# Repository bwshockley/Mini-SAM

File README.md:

# Mini SAM
Mini SAM is a LEGO® minifigure-sized development board based on either the Microchip SAMD51G 48-Pin 32-Bit ARM® Cortex®-M4F MCU (Mini SAM M4) or the Microchip SAMD21G 48-Pin 32-Bit ARM® Cortex®-M0+ MCU running at 48Mhz.

## Board Features

### I/O
The boards includes a usb-micro interface for programming and power.   Around the edge are 0.050" spaced holes with castellations outside of that and the plan is to have a "breakout" board with standard .100" headers.  There is an optional board design in work that will be 4-layer and have the .100" smt header pads included.

The Mini SAM boards include two LED indicators; a standard "Built-In" LED and an APA102 RGB LED.  There are two built-in buttons as well; a RESET button and a user programmable BUTTON.

### Memory
In order to support CircuitPython, a 2MB Quad-SPI flash memory chip is included.  This provides plenty of space for the CircuitPython program as well as space for user programming.

### Other
The boards include a 600mA 3.3V regulator, more than enough to power this little board and its built-in features.  The micro-USB circuitry includes optional provisioning for case grounding and ESD protection.  Finally, The AREF input and recommended Analog and Digital power separation is present on the board.

## BOM
Please see the BOM for each board

## Bootloader
A UF2 bootloader is available for the M4 board (will be available for the M0 when ready).  This bootloader may be built from source using my UF2 repository or downloaded from the [Minifigboards Software](https://www.minifigboards.com/mini-sam-m4/software/) page.

Source: [UF2-SAMDX1](https://github.com/bwshockley/uf2-samdx1) 

## Arduino
Arduino firmware is available for the M4 board as well. Instructions for adding the board to the board manager in the Arduino IDE are available on the [Minifigboards Software](https://www.minifigboards.com/mini-sam-m4/software/) page.

## CircuitPython
CircuitPython is available for the M4 board. [Mini SAM M4](https://circuitpython.org/board/mini_sam_m4/)  
CircuitPython will soon be available for the M0 board.

## Open Source
Boards can be ordered direct from [OSHPark](https://oshpark.com/profiles/bwshockley).

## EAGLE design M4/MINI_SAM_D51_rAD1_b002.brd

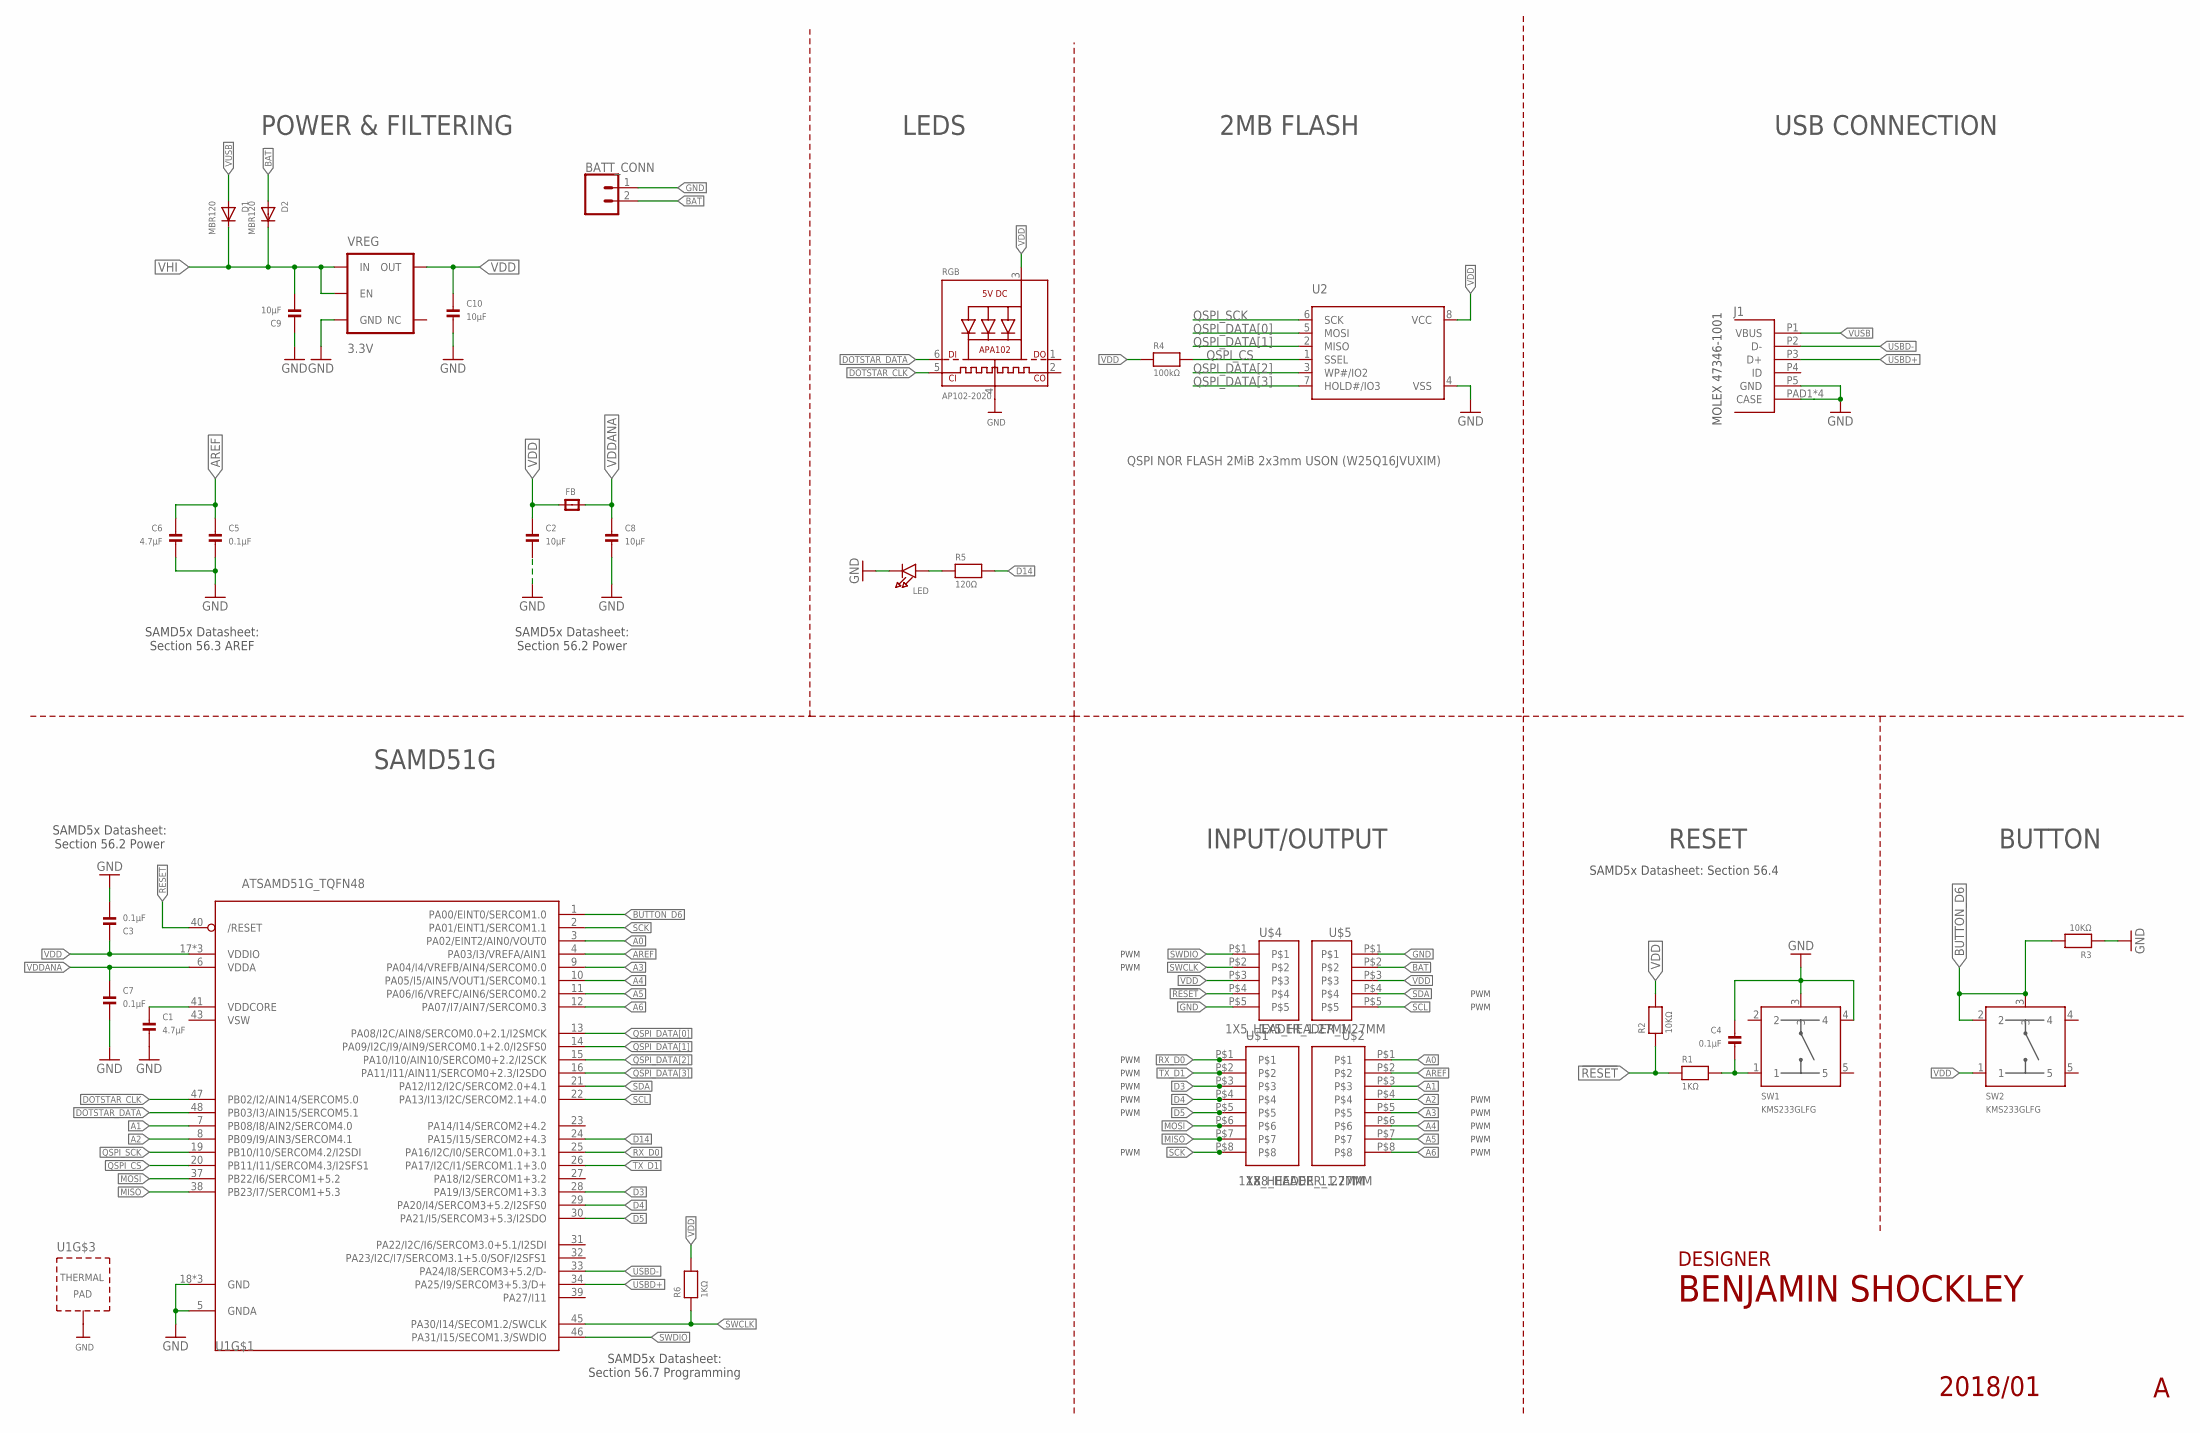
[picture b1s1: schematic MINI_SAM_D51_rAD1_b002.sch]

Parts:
BATT_CONN: CONN_02-JST-2MM-SMT; JST-2-SMD_NO_PASTE
C1, C6: 4.7µF; 0603_CAPACITOR
C2, C8, C9, C10: 10µF; 0603_CAPACITOR
C3, C4, C5, C7: 0.1µF; 0603_CAPACITOR
D1, D2: MBR120; SOD-123FL
FB: Impedence: 50 ohm @ 20 MHz, 220 Ohm @ 100 MHz; lo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; 0603_INDUCTOR
J1: MOLEX_47346-100147346; MOLEX_47346-1001
LED: VLRK31Q1R2-GS08; REVERSE_MOUNT_LED
R1, R6: 1KΩ; 0603_RESISTOR
R2, R3: 10KΩ; 0603_RESISTOR
R4: 100kΩ; 0603_RESISTOR
R5: 120Ω; 0603_RESISTOR
RGB: AP102-2020; APA102_2020
SW1, SW2: KMS233GLFG; KMS_SWITCH
U1: ATSAMD51G_TQFN48; TQFN48_7MM
U2: QSPI NOR FLASH 2MiB 2x3mm USON (W25Q16JVUXIM); USON8
U$1, U$2: 1X8_HEADER_1.27MM
U$4, U$5: 1X5_HEADER_1.27MM
VREG: 3.3V; SOT23-5

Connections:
!RESET: R1.1, R2.1, U1.40 (/RESET), U$4.P$4
A0: U1.3 (PA02/EINT2/AIN0/VOUT0), U$2.P$1
A1: U1.7 (PB08/I8/AIN2/SERCOM4.0), U$2.P$3
A2: U1.8 (PB09/I9/AIN3/SERCOM4.1), U$2.P$4
A3: U1.9 (PA04/I4/VREFB/AIN4/SERCOM0.0), U$2.P$5
A4: U1.10 (PA05/I5/AIN5/VOUT1/SERCOM0.1), U$2.P$6
A5: U1.11 (PA06/I6/VREFC/AIN6/SERCOM0.2), U$2.P$7
A6: U1.12 (PA07/I7/AIN7/SERCOM0.3), U$2.P$8
AREF: C5.1, C6.1, U1.4 (PA03/I3/VREFA/AIN1), U$2.P$2
BAT: BATT_CONN.2 (1), D2.A, U$5.P$2
BUTTON_D6: R3.2, SW2.2, SW2.3, U1.1 (PA00/EINT0/SERCOM1.0)
D3: U1.28 (PA19/I3/SERCOM1+3.3), U$1.P$3
D4: U1.29 (PA20/I4/SERCOM3+5.2/I2SFS0), U$1.P$4
D5: U1.30 (PA21/I5/SERCOM3+5.3/I2SDO), U$1.P$5
D14: R5.2, U1.24 (PA15/I15/SERCOM2+4.3)
DOTSTAR_CLK: RGB.5 (CKI), U1.47 (PB02/I2/AIN14/SERCOM5.0)
DOTSTAR_DATA: RGB.6 (DI), U1.48 (PB03/I3/AIN15/SERCOM5.1)
GND: BATT_CONN.1 (2), C1.2, C2.2, C3.2, C4.1, C5.2, C6.2, C7.2, C8.2, C9.1, C10.2, J1.P5 (GND), J1.PAD1 (CASE), J1.PAD2 (CASE), J1.PAD3 (CASE), J1.PAD4 (CASE), LED.C, R3.1, RGB.4 (GND), SW1.3, SW1.4, U1.5 (GNDA), U1.18 (GND), U1.35 (GND), U1.42 (GND), U1.THERMAL (TP), U2.4 (VSS), U$4.P$5, U$5.P$1, VREG.2 (GND)
MISO: U1.38 (PB23/I7/SERCOM1+5.3), U$1.P$7
MOSI: U1.37 (PB22/I6/SERCOM1+5.2), U$1.P$6
unnamed: LED.A, R5.1
unnamed: C4.2, R1.2, SW1.1
unnamed: C1.1, U1.41 (VDDCORE)
QSPI_CS: R4.2, U1.20 (PB11/I11/SERCOM4.3/I2SFS1), U2.1 (SSEL)
QSPI_DATA[0]: U1.13 (PA08/I2C/AIN8/SERCOM0.0+2.1/I2SMCK), U2.5 (MOSI)
QSPI_DATA[1]: U1.14 (PA09/I2C/I9/AIN9/SERCOM0.1+2.0/I2SFS0), U2.2 (MISO)
QSPI_DATA[2]: U1.15 (PA10/I10/AIN10/SERCOM0+2.2/I2SCK), U2.3 (WP#/IO2)
QSPI_DATA[3]: U1.16 (PA11/I11/AIN11/SERCOM0+2.3/I2SDO), U2.7 (HOLD#/IO3)
QSPI_SCK: U1.19 (PB10/I10/SERCOM4.2/I2SDI), U2.6 (SCK)
RX_D0: U1.25 (PA16/I2C/I0/SERCOM1.0+3.1), U$1.P$1
SCK: U1.2 (PA01/EINT1/SERCOM1.1), U$1.P$8
SCL: U1.22 (PA13/I13/I2C/SERCOM2.1+4.0), U$5.P$5
SDA: U1.21 (PA12/I12/I2C/SERCOM2.0+4.1), U$5.P$4
SWCLK: R6.1, U1.45 (PA30/I14/SECOM1.2/SWCLK), U$4.P$2
SWDIO: U1.46 (PA31/I15/SECOM1.3/SWDIO), U$4.P$1
TX_D1: U1.26 (PA17/I2C/I1/SERCOM1.1+3.0), U$1.P$2
USBD+: J1.P3 (D+), U1.34 (PA25/I9/SERCOM3+5.3/D+)
USBD-: J1.P2 (D-), U1.33 (PA24/I8/SERCOM3+5.2/D-)
VDD: C2.1, C3.1, C10.1, FB.1, R2.2, R4.1, R6.2, RGB.3 (VDD), SW2.1, U1.17 (VDDIO), U1.36 (VDDIO), U1.44 (VDDIO), U2.8 (VCC), U$4.P$3, U$5.P$3, VREG.5 (OUT)
VDDANA: C7.1, C8.1, FB.2, U1.6 (VDDA)
VHI: C9.2, D1.C, D2.C, VREG.1 (IN), VREG.3 (EN)
VSW: U1.43 (VSW)
VUSB: D1.A, J1.P1 (VBUS)

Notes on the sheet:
INPUT/OUTPUT
RESET
POWER & FILTERING
SAMD51G
LEDS
USB CONNECTION
MOLEX 47346-1001
BUTTON
DESIGNER
SAMD5x Datasheet: Section 56.4
2MB FLASH
SAMD5x Datasheet: Section 56.3 AREF
SAMD5x Datasheet: Section 56.2 Power
SAMD5x Datasheet: Section 56.7 Programming
PWM

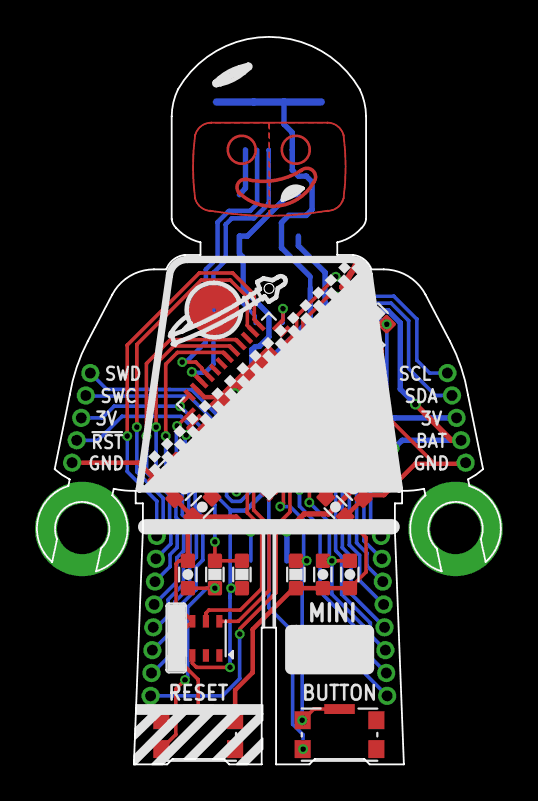
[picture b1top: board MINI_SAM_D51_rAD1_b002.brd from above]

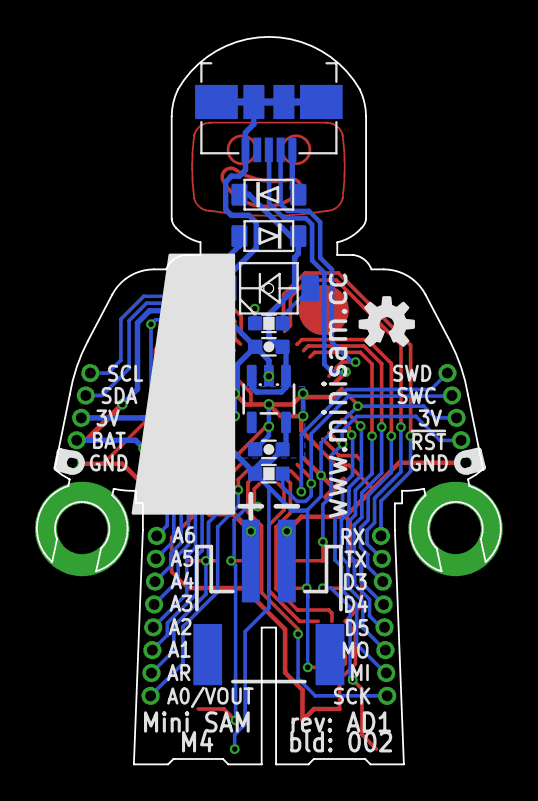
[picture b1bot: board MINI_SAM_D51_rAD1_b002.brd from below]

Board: 2 copper layers, 25.8 x 40.4 mm, 33 parts (11 on the bottom side), 42 nets.

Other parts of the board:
U$3: OSHW-LOGO-S

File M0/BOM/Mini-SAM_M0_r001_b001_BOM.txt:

Qty Value                                                            Device                Package                       Parts           Description                                 PROD_ID    VALUE
4   0.1µF                                                            CAP_CERAMIC_0603MP    _0603MP                       C3, C4, C6, C8  Ceramic Capacitors                                          
1   100kO                                                            RESISTOR_0603MP       _0603MP                       R4              Resistors                                                   
2   10KO                                                             RESISTOR_0603MP       _0603MP                       R2, R3          Resistors                                                   
4   10µF                                                             CAP_CERAMIC_0603MP    _0603MP                       C2, C7, C9, C10 Ceramic Capacitors                                          
2   1KO                                                              RESISTOR_0603MP       _0603MP                       R1, R6          Resistors                                                   
2   1X5_HEADER_1.27MMCAST                                            1X5_HEADER_1.27MMCAST 1X5_HEADER_1.27MM_CASTELLATED J2, J4                                                                      
2   1X8_HEADER_1.27MMCAST                                            1X8_HEADER_1.27MMCAST 1X8_HEADER_1.27MM_CASTELLATED J3, J5                                                                      
1   220O                                                             RESISTOR_0603MP       _0603MP                       R5              Resistors                                                   
2   4.7µF                                                            CAP_CERAMIC_0603MP    _0603MP                       C1, C5          Ceramic Capacitors                                          
1   AP102-2020                                                       APA1022020            APA102_2020                   RGB             APA102/DotStar Pixels                                       
1   AP2112K-3.3V                                                     V_REG_AP2112K-3.3V    SOT23-5                       VREG            AP2112 - 600mA CMOS LDO Regulator w/ Enable VREG-12457 3.3V 
1   ATSAMD21G18                                                      ATSAMD21G_QFN         TQFN48_7MM                    U1                                                                          
1   Easily mounted up-sdie down.                                     LED0805_NOOUTLINE     CHIPLED_0805_NOOUTLINE        LED             LED                                                         
1   Impedence: 50 ohm @ 20 MHz, 220 Ohm @ 100 MHz; low DC resistance FERRITE_0603MP        _0603MP                       FB              Ferrite Bead                                                
2   KMS233GLFG                                                       KMS_SWITCHKMS         KMS_SWITCH                    SW1, SW2                                                                    
2   MBR120                                                           DIODE_SOD-123FL       SOD-123FL                     D1, D2          Diode                                                       
1   MOLEX_47346-100147346                                            MOLEX_47346-100147346 MOLEX_47346-1001              J1                                                                          
1   flash                                                            SPIFLASH_8PINUX       USON8                         U3              SOIC8 SPI Flash

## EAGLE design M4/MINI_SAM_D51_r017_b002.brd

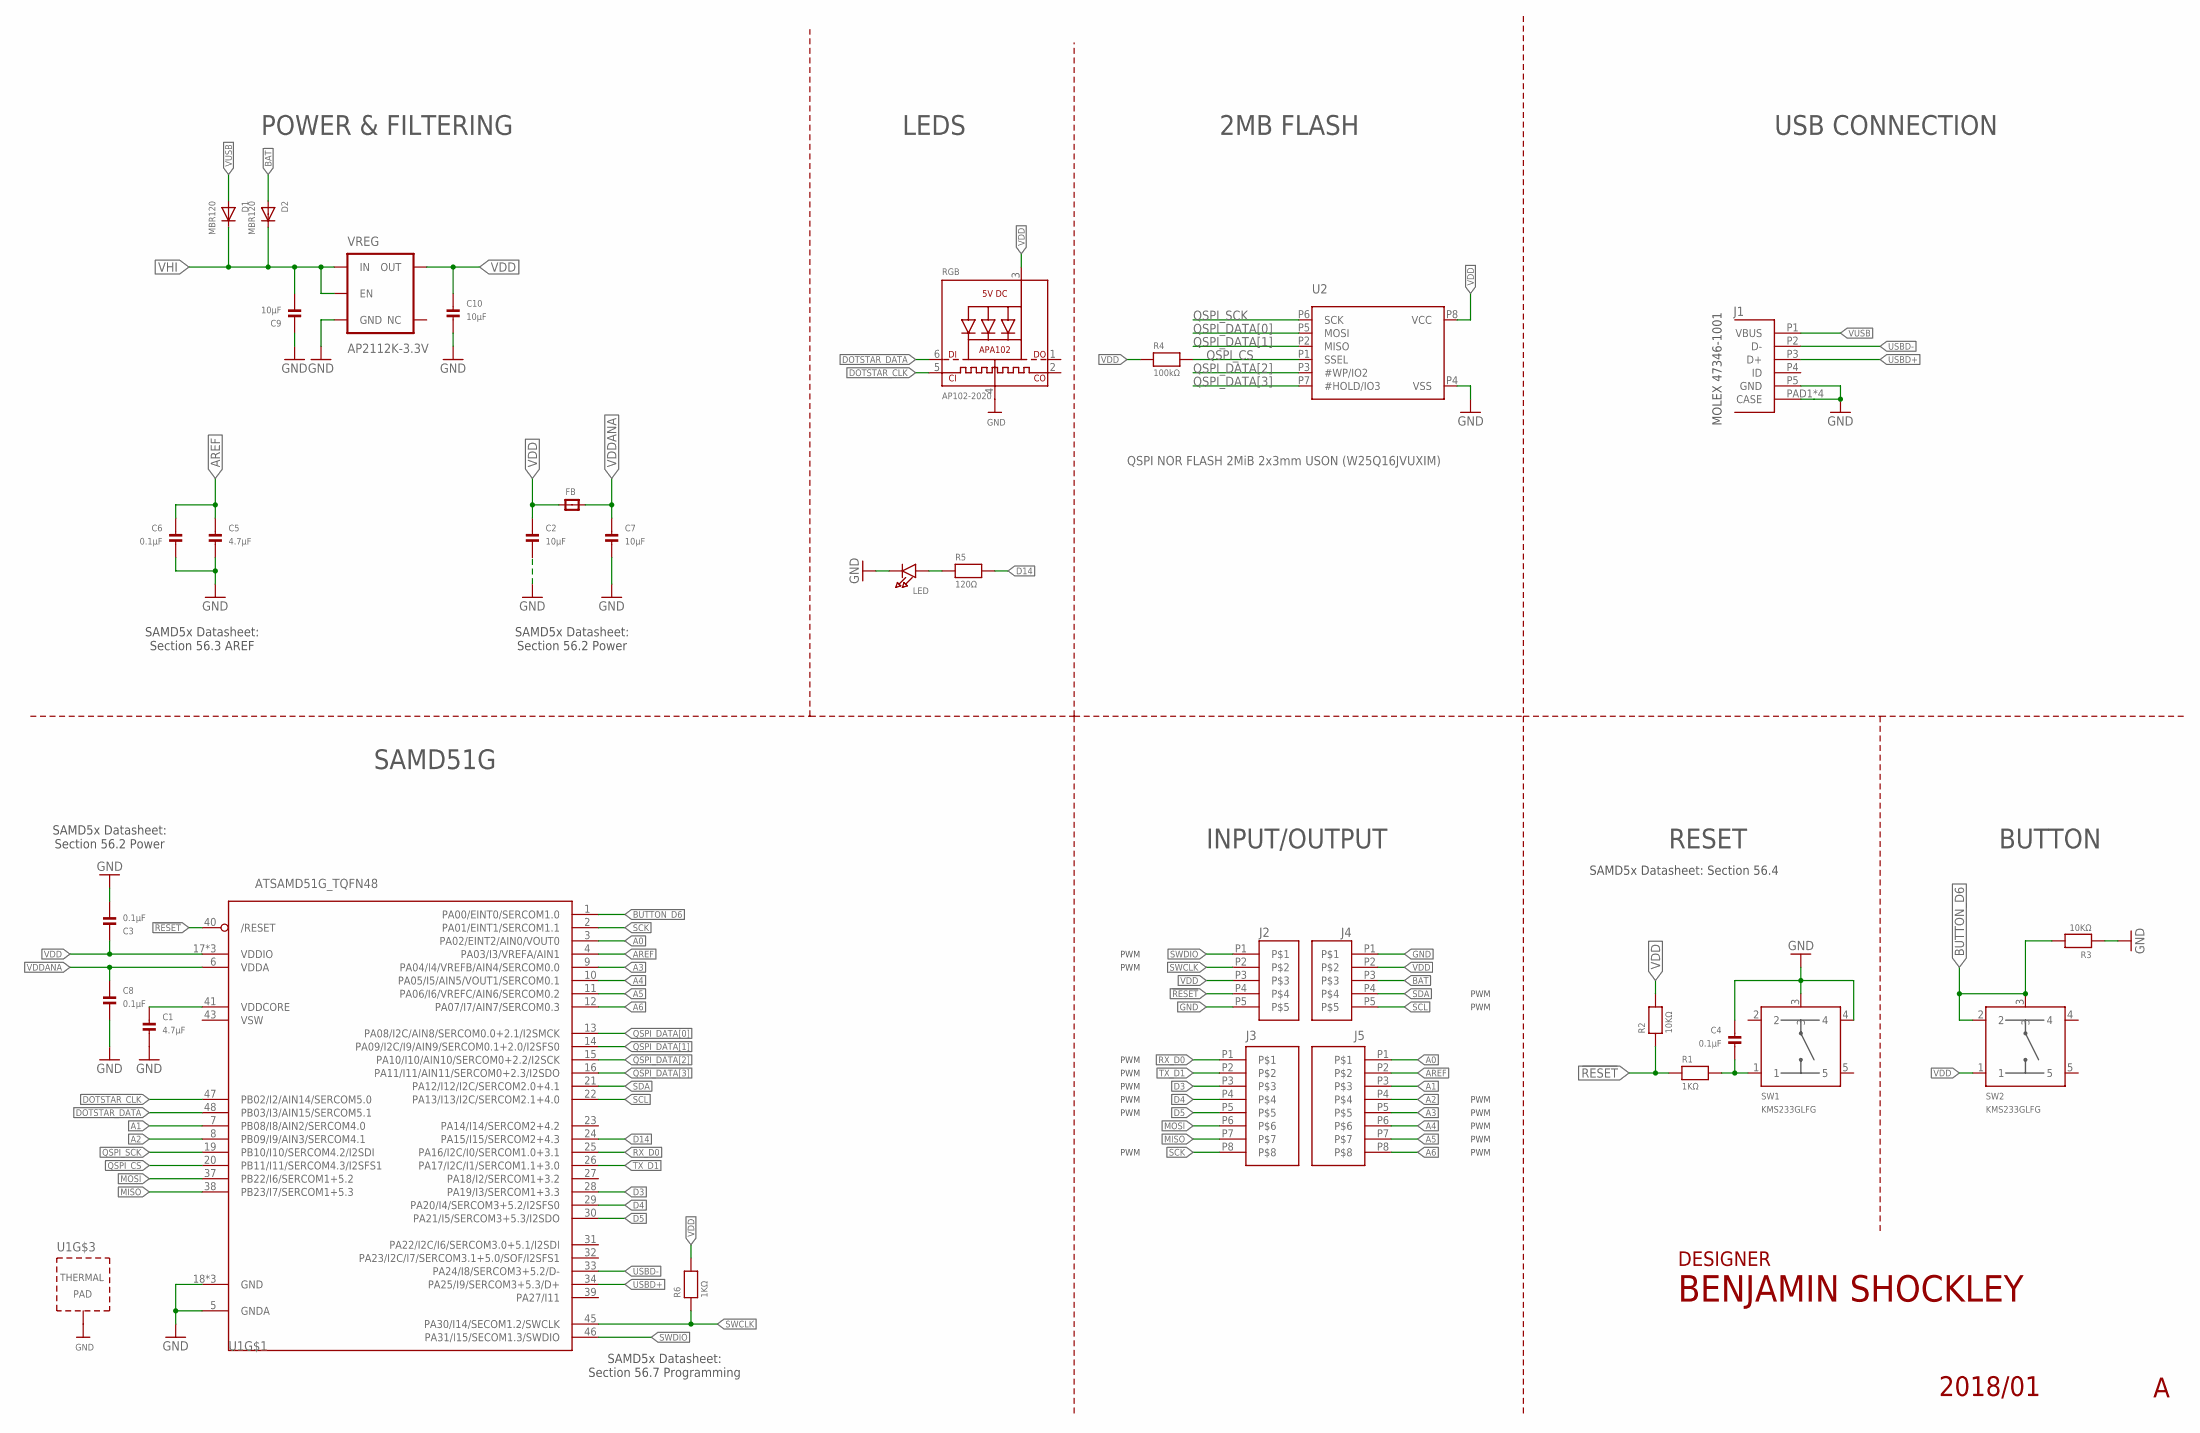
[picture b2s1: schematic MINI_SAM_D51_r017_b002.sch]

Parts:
C1, C5: 4.7µF; _0603MP
C2, C7, C9, C10: 10µF; _0603MP
C3, C4, C6, C8: 0.1µF; _0603MP
D1, D2: MBR120; SOD-123FL
FB: Impedence: 50 ohm @ 20 MHz, 220 Ohm @ 100 MHz; lo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; _0603MP
J1: MOLEX_47346-100147346; MOLEX_47346-1001
J2, J4: 1X5_HEADER_1.27MMCAST; 1X5_HEADER_1.27MM_CASTELLATED
J3, J5: 1X8_HEADER_1.27MMCAST; 1X8_HEADER_1.27MM_CASTELLATED
LED: VLRK31Q1R2-GS08; REVERSE_MOUNT_LED
R1, R6: 1KΩ; _0603MP
R2, R3: 10KΩ; _0603MP
R4: 100kΩ; _0603MP
R5: 120Ω; _0603MP
RGB: AP102-2020; APA102_2020
SW1, SW2: KMS233GLFG; KMS_SWITCH
U1: ATSAMD51G_TQFN48; TQFN48_7MM
U2: QSPI NOR FLASH 2MiB 2x3mm USON (W25Q16JVUXIM); USON4X3
VREG: AP2112K-3.3V; SOT23-5

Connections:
!RESET: J2.P4, R1.1, R2.1, U1.40 (/RESET)
A0: J5.P1, U1.3 (PA02/EINT2/AIN0/VOUT0)
A1: J5.P3, U1.7 (PB08/I8/AIN2/SERCOM4.0)
A2: J5.P4, U1.8 (PB09/I9/AIN3/SERCOM4.1)
A3: J5.P5, U1.9 (PA04/I4/VREFB/AIN4/SERCOM0.0)
A4: J5.P6, U1.10 (PA05/I5/AIN5/VOUT1/SERCOM0.1)
A5: J5.P7, U1.11 (PA06/I6/VREFC/AIN6/SERCOM0.2)
A6: J5.P8, U1.12 (PA07/I7/AIN7/SERCOM0.3)
AREF: C5.1, C6.1, J5.P2, U1.4 (PA03/I3/VREFA/AIN1)
BAT: D2.A, J4.P3
BUTTON_D6: R3.2, SW2.2, SW2.3, U1.1 (PA00/EINT0/SERCOM1.0)
D3: J3.P3, U1.28 (PA19/I3/SERCOM1+3.3)
D4: J3.P4, U1.29 (PA20/I4/SERCOM3+5.2/I2SFS0)
D5: J3.P5, U1.30 (PA21/I5/SERCOM3+5.3/I2SDO)
D14: R5.2, U1.24 (PA15/I15/SERCOM2+4.3)
DOTSTAR_CLK: RGB.5 (CKI), U1.47 (PB02/I2/AIN14/SERCOM5.0)
DOTSTAR_DATA: RGB.6 (DI), U1.48 (PB03/I3/AIN15/SERCOM5.1)
GND: C1.2, C2.2, C3.2, C4.1, C5.2, C6.2, C7.2, C8.2, C9.1, C10.2, J1.P5 (GND), J1.PAD1 (CASE), J1.PAD2 (CASE), J1.PAD3 (CASE), J1.PAD4 (CASE), J2.P5, J4.P1, LED.C, R3.1, RGB.4 (GND), SW1.3, SW1.4, U1.5 (GNDA), U1.18 (GND), U1.35 (GND), U1.42 (GND), U1.THERMAL (TP), U2.P4 (VSS), VREG.2 (GND)
MISO: J3.P7, U1.38 (PB23/I7/SERCOM1+5.3)
MOSI: J3.P6, U1.37 (PB22/I6/SERCOM1+5.2)
unnamed: LED.A, R5.1
unnamed: C4.2, R1.2, SW1.1
unnamed: C1.1, U1.41 (VDDCORE)
QSPI_CS: R4.2, U1.20 (PB11/I11/SERCOM4.3/I2SFS1), U2.P1 (SSEL)
QSPI_DATA[0]: U1.13 (PA08/I2C/AIN8/SERCOM0.0+2.1/I2SMCK), U2.P5 (MOSI)
QSPI_DATA[1]: U1.14 (PA09/I2C/I9/AIN9/SERCOM0.1+2.0/I2SFS0), U2.P2 (MISO)
QSPI_DATA[2]: U1.15 (PA10/I10/AIN10/SERCOM0+2.2/I2SCK), U2.P3 (#WP/IO2)
QSPI_DATA[3]: U1.16 (PA11/I11/AIN11/SERCOM0+2.3/I2SDO), U2.P7 (#HOLD/IO3)
QSPI_SCK: U1.19 (PB10/I10/SERCOM4.2/I2SDI), U2.P6 (SCK)
RX_D0: J3.P1, U1.25 (PA16/I2C/I0/SERCOM1.0+3.1)
SCK: J3.P8, U1.2 (PA01/EINT1/SERCOM1.1)
SCL: J4.P5, U1.22 (PA13/I13/I2C/SERCOM2.1+4.0)
SDA: J4.P4, U1.21 (PA12/I12/I2C/SERCOM2.0+4.1)
SWCLK: J2.P2, R6.1, U1.45 (PA30/I14/SECOM1.2/SWCLK)
SWDIO: J2.P1, U1.46 (PA31/I15/SECOM1.3/SWDIO)
TX_D1: J3.P2, U1.26 (PA17/I2C/I1/SERCOM1.1+3.0)
USBD+: J1.P3 (D+), U1.34 (PA25/I9/SERCOM3+5.3/D+)
USBD-: J1.P2 (D-), U1.33 (PA24/I8/SERCOM3+5.2/D-)
VDD: C2.1, C3.1, C10.1, FB.1, J2.P3, J4.P2, R2.2, R4.1, R6.2, RGB.3 (VDD), SW2.1, U1.17 (VDDIO), U1.36 (VDDIO), U1.44 (VDDIO), U2.P8 (VCC), VREG.5 (OUT)
VDDANA: C7.1, C8.1, FB.2, U1.6 (VDDA)
VHI: C9.2, D1.C, D2.C, VREG.1 (IN), VREG.3 (EN)
VSW: U1.43 (VSW)
VUSB: D1.A, J1.P1 (VBUS)

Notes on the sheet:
INPUT/OUTPUT
RESET
POWER & FILTERING
SAMD51G
LEDS
USB CONNECTION
MOLEX 47346-1001
BUTTON
DESIGNER
SAMD5x Datasheet: Section 56.4
2MB FLASH
SAMD5x Datasheet: Section 56.3 AREF
SAMD5x Datasheet: Section 56.2 Power
SAMD5x Datasheet: Section 56.7 Programming
PWM

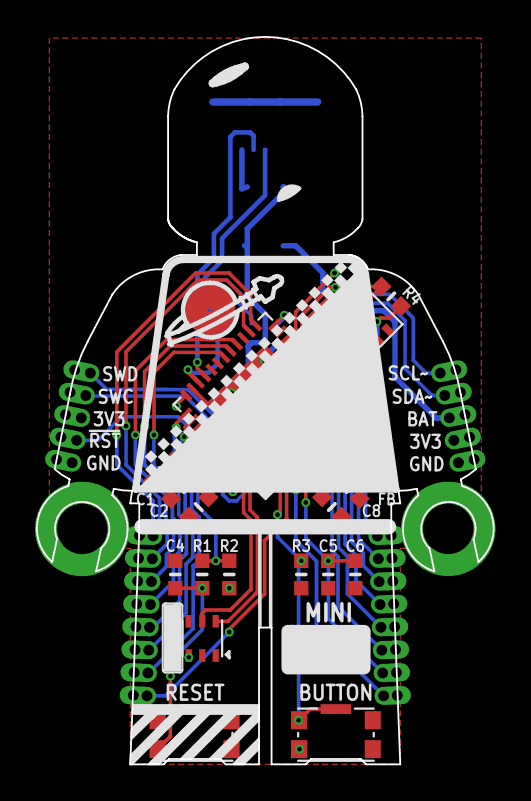
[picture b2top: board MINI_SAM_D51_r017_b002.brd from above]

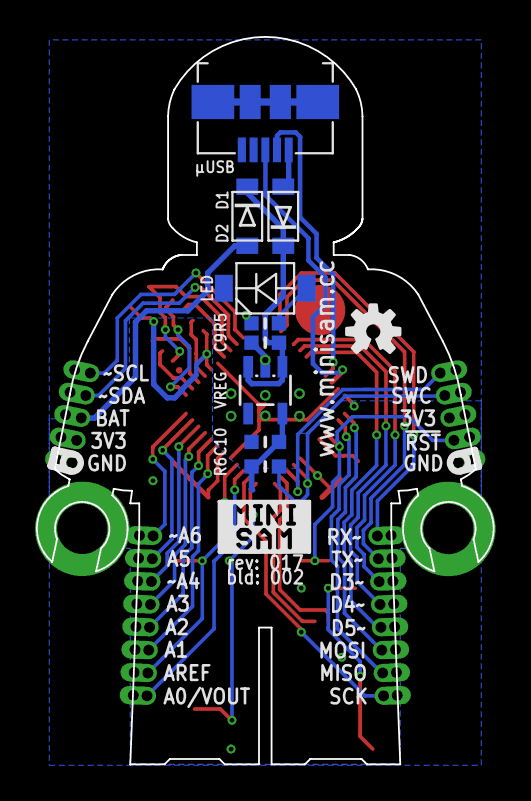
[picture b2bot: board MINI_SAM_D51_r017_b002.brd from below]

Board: 2 copper layers, 25.4 x 40.4 mm, 32 parts (10 on the bottom side), 42 nets.

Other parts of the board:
U$3: OSHW-LOGO-S

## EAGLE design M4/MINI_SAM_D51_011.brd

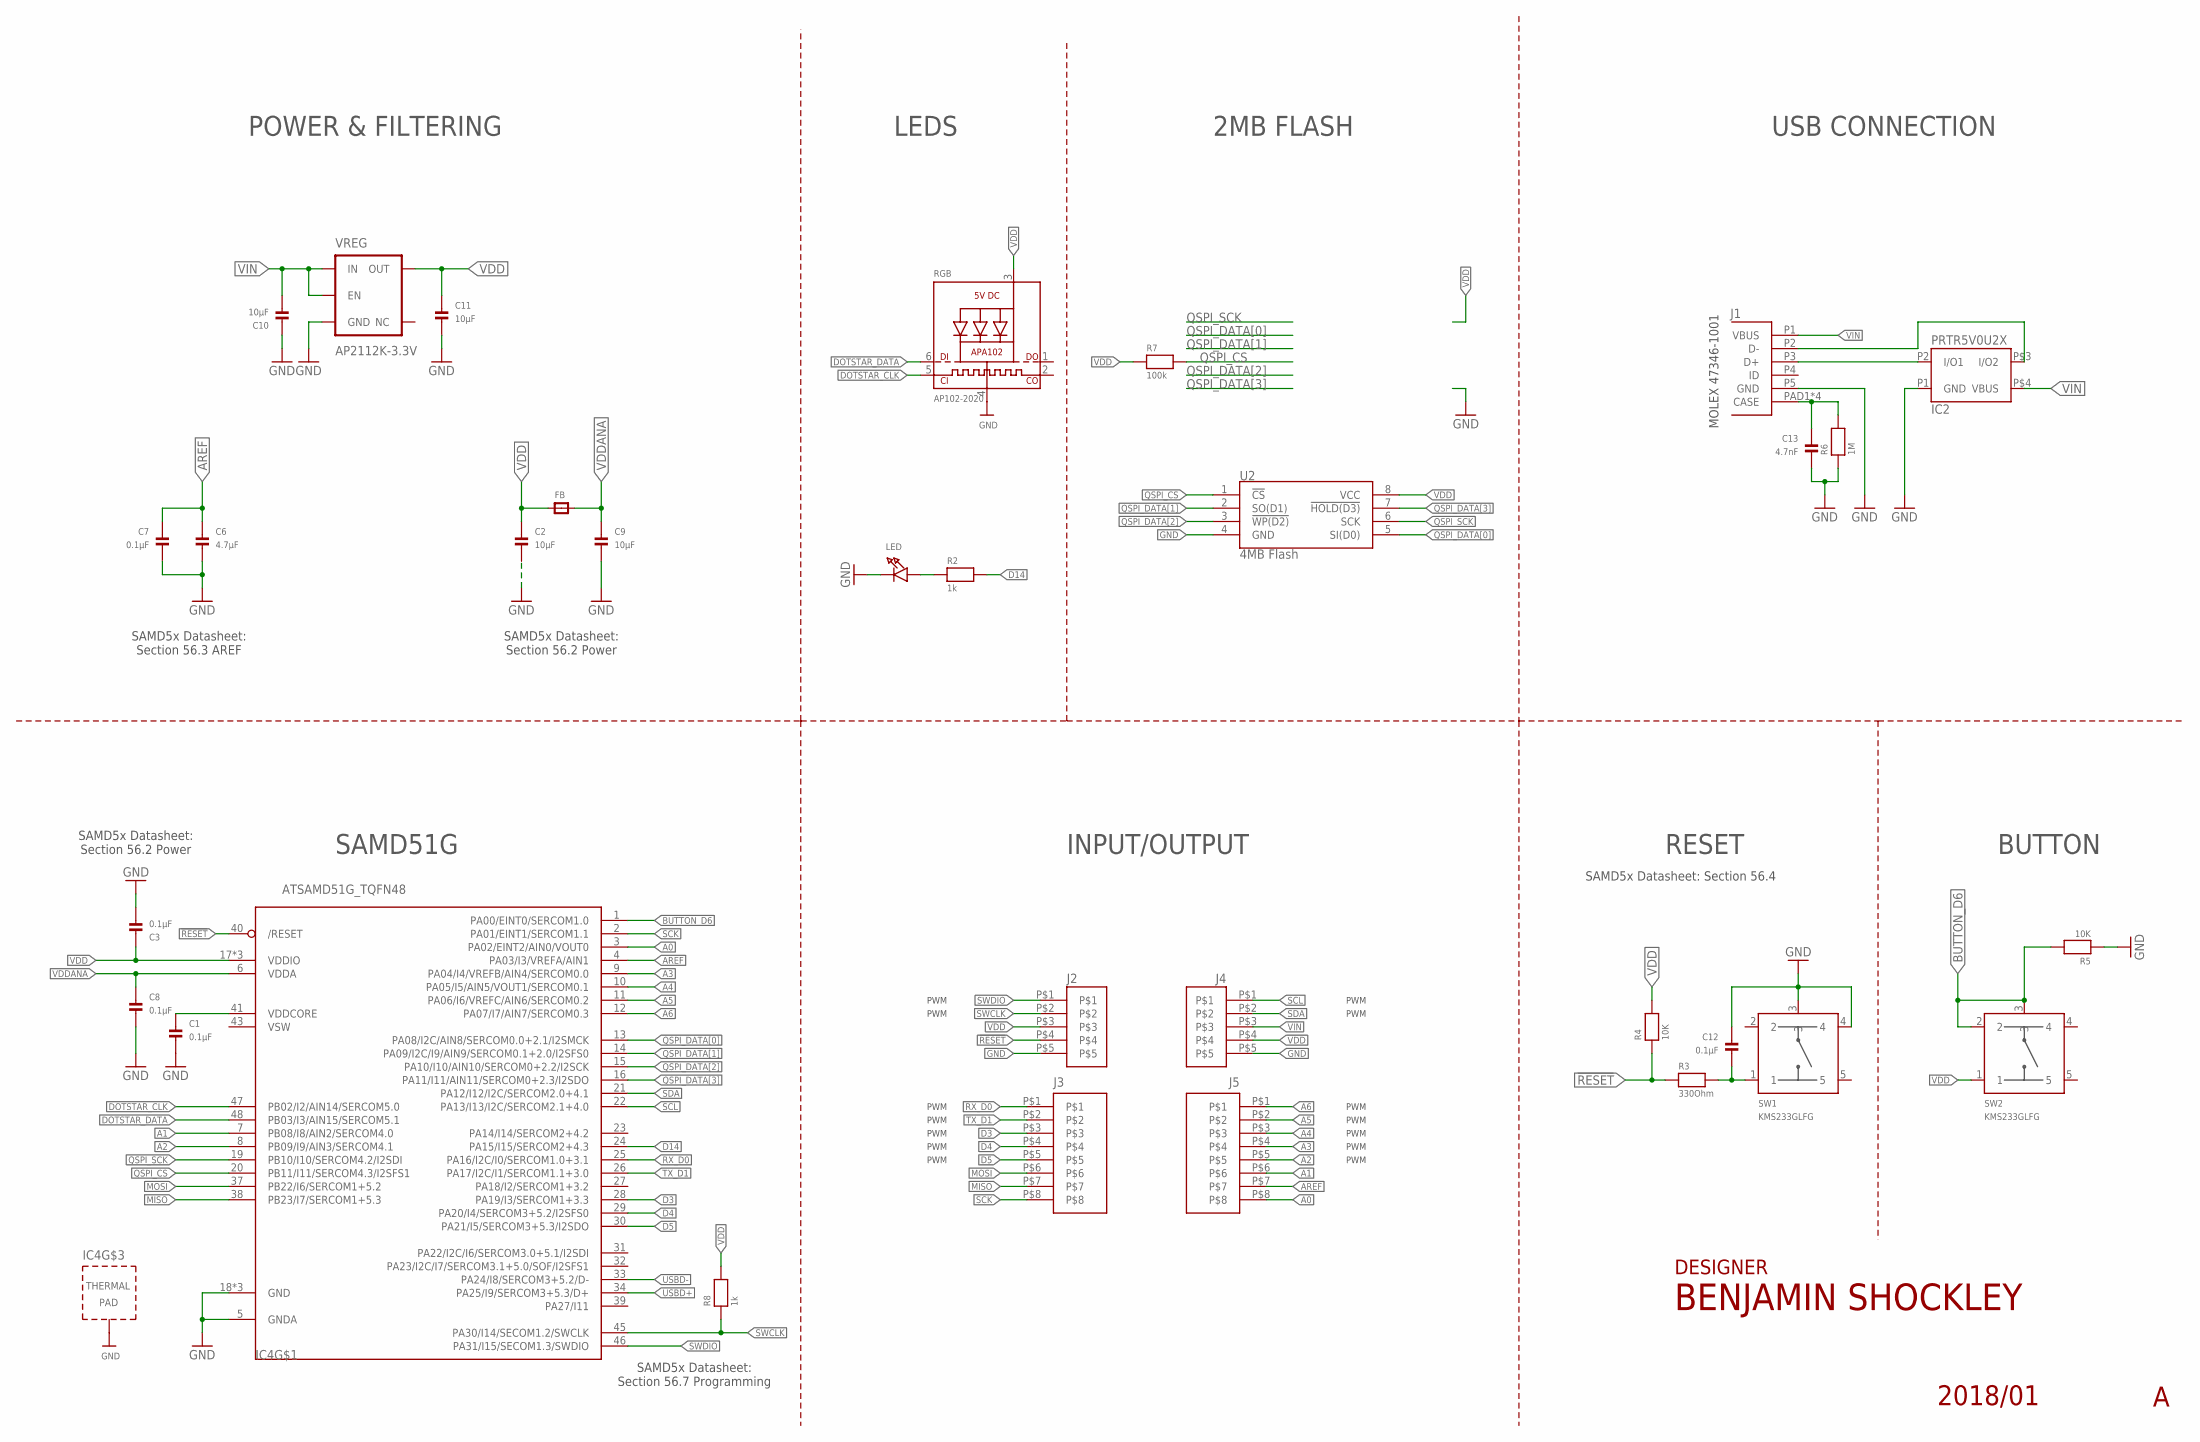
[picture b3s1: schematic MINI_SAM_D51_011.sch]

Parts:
C1, C3, C7, C8, C12: 0.1µF; _0603MP
C2, C9, C10, C11: 10µF; _0603MP
C6: 4.7µF; _0603MP
C13: 4.7nF; _0603MP
FB: FERRITE_0603MP; _0603MP
IC2: PRTR5V0U2X; SOT143B_REFLOW
IC4: ATSAMD51G_TQFN48; TQFN48_7MM
J1: MOLEX_47346-100147346; MOLEX_47346-1001
J2, J4: 1X5_HEADER_1.27MM
J3, J5: 1X8_HEADER_1.27MM
LED: LED0805_NOOUTLINE; CHIPLED_0805_NOOUTLINE
R2, R8: 1k; _0603MP
R3: 330Ohm; _0603MP
R4, R5: 10K; _0603MP
R6: 1M; _0603MP
R7: 100k; _0603MP
RGB: AP102-2020; APA102_2020
SW1, SW2: KMS233GLFG; KMS_SWITCH
U2: 4MB Flash; SO08
VREG: AP2112K-3.3V; SOT23-5

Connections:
!RESET: IC4.40 (/RESET), J2.P$4, R3.1, R4.1
A0: IC4.3 (PA02/EINT2/AIN0/VOUT0), J5.P$8
A1: IC4.7 (PB08/I8/AIN2/SERCOM4.0), J5.P$6
A2: IC4.8 (PB09/I9/AIN3/SERCOM4.1), J5.P$5
A3: IC4.9 (PA04/I4/VREFB/AIN4/SERCOM0.0), J5.P$4
A4: IC4.10 (PA05/I5/AIN5/VOUT1/SERCOM0.1), J5.P$3
A5: IC4.11 (PA06/I6/VREFC/AIN6/SERCOM0.2), J5.P$2
A6: IC4.12 (PA07/I7/AIN7/SERCOM0.3), J5.P$1
AREF: C6.1, C7.1, IC4.4 (PA03/I3/VREFA/AIN1), J5.P$7
BUTTON_D6: IC4.1 (PA00/EINT0/SERCOM1.0), R5.2, SW2.2, SW2.3
D3: IC4.28 (PA19/I3/SERCOM1+3.3), J3.P$3
D4: IC4.29 (PA20/I4/SERCOM3+5.2/I2SFS0), J3.P$4
D5: IC4.30 (PA21/I5/SERCOM3+5.3/I2SDO), J3.P$5
D14: IC4.24 (PA15/I15/SERCOM2+4.3), R2.2
DOTSTAR_CLK: IC4.47 (PB02/I2/AIN14/SERCOM5.0), RGB.5 (CKI)
DOTSTAR_DATA: IC4.48 (PB03/I3/AIN15/SERCOM5.1), RGB.6 (DI)
GND: C1.2, C2.2, C3.2, C6.2, C7.2, C8.2, C9.2, C10.1, C11.2, C12.1, C13.2, IC2.P1 (GND), IC4.5 (GNDA), IC4.18 (GND), IC4.35 (GND), IC4.42 (GND), IC4.THERMAL (TP), J1.P5 (GND), J2.P$5, J4.P$5, LED.C, R5.1, R6.1, RGB.4 (GND), SW1.3, SW1.4, U2.4 (GND), VREG.2 (GND)
MISO: IC4.38 (PB23/I7/SERCOM1+5.3), J3.P$7
MOSI: IC4.37 (PB22/I6/SERCOM1+5.2), J3.P$6
unnamed: C13.1, J1.PAD1 (CASE), J1.PAD2 (CASE), J1.PAD3 (CASE), J1.PAD4 (CASE), R6.2
unnamed: LED.A, R2.1
unnamed: C12.2, R3.2, SW1.1
unnamed: C1.1, IC4.41 (VDDCORE)
QSPI_CS: IC4.20 (PB11/I11/SERCOM4.3/I2SFS1), R7.2, U2.1 (!CS)
QSPI_DATA[0]: IC4.13 (PA08/I2C/AIN8/SERCOM0.0+2.1/I2SMCK), U2.5 (SI(D0))
QSPI_DATA[1]: IC4.14 (PA09/I2C/I9/AIN9/SERCOM0.1+2.0/I2SFS0), U2.2 (SO(D1))
QSPI_DATA[2]: IC4.15 (PA10/I10/AIN10/SERCOM0+2.2/I2SCK), U2.3 (!WP(D2))
QSPI_DATA[3]: IC4.16 (PA11/I11/AIN11/SERCOM0+2.3/I2SDO), U2.7 (!HOLD(D3))
QSPI_SCK: IC4.19 (PB10/I10/SERCOM4.2/I2SDI), U2.6 (SCK)
RX_D0: IC4.25 (PA16/I2C/I0/SERCOM1.0+3.1), J3.P$1
SCK: IC4.2 (PA01/EINT1/SERCOM1.1), J3.P$8
SCL: IC4.22 (PA13/I13/I2C/SERCOM2.1+4.0), J4.P$1
SDA: IC4.21 (PA12/I12/I2C/SERCOM2.0+4.1), J4.P$2
SWCLK: IC4.45 (PA30/I14/SECOM1.2/SWCLK), J2.P$2, R8.1
SWDIO: IC4.46 (PA31/I15/SECOM1.3/SWDIO), J2.P$1
TX_D1: IC4.26 (PA17/I2C/I1/SERCOM1.1+3.0), J3.P$2
USBD+: IC2.P2 (I/O1), IC4.34 (PA25/I9/SERCOM3+5.3/D+), J1.P3 (D+)
USBD-: IC2.P$3 (I/O2), IC4.33 (PA24/I8/SERCOM3+5.2/D-), J1.P2 (D-)
VDD: C2.1, C3.1, C11.1, FB.1, IC4.17 (VDDIO), IC4.36 (VDDIO), IC4.44 (VDDIO), J2.P$3, J4.P$4, R4.2, R7.1, R8.2, RGB.3 (VDD), SW2.1, U2.8 (VCC), VREG.5 (OUT)
VDDANA: C8.1, C9.1, FB.2, IC4.6 (VDDA)
VIN: C10.2, IC2.P$4 (VBUS), J1.P1 (VBUS), J4.P$3, VREG.1 (IN), VREG.3 (EN)
VSW: IC4.43 (VSW)

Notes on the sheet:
INPUT/OUTPUT
RESET
POWER & FILTERING
SAMD51G
LEDS
USB CONNECTION
MOLEX 47346-1001
BUTTON
DESIGNER
SAMD5x Datasheet: Section 56.4
2MB FLASH
SAMD5x Datasheet: Section 56.3 AREF
SAMD5x Datasheet: Section 56.2 Power
SAMD5x Datasheet: Section 56.7 Programming
PWM

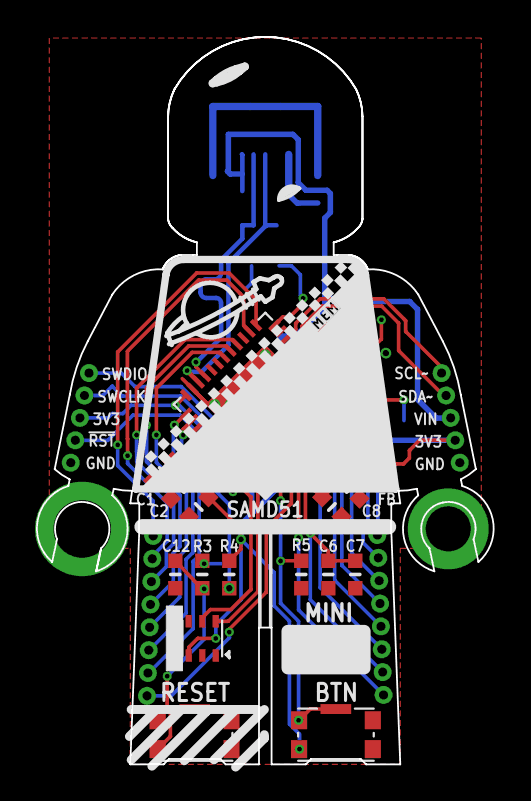
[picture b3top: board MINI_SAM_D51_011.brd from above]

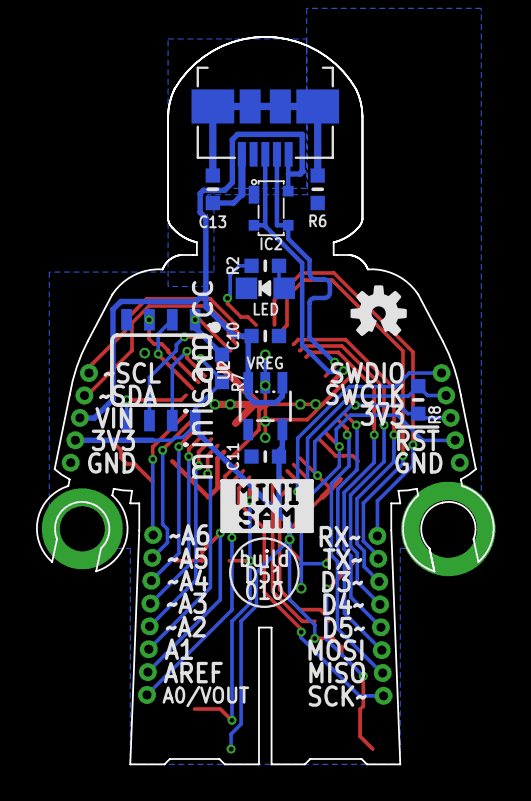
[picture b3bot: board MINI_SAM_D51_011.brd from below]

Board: 2 copper layers, 25.4 x 40.4 mm, 33 parts (13 on the bottom side), 41 nets.

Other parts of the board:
U$3: OSHW-LOGO-S

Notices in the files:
parts and their libraries:
SparkFun-Aesthetics: Licensing: Creative Commons ShareAlike 4.0 International - https://creativecommons.org/licenses/by-sa/4.0
microbuilder: This work is placed in the public domain, and may be freely used for commercial and non-commercial work with the following conditions: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
